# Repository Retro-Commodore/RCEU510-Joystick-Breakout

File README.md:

# RCEU510-Joystick-Breakout
 RCEU510 - Joystick breakout for diagnostics or development purposes

# BOM
1x DB9 Male (for wire)
1x DB9 Female (for wire)
1x 2x5 or 2x 1x5 SIL header

# Description
This little adapter can be used to measure signals (i.e. mouse movements) or diagnostics.

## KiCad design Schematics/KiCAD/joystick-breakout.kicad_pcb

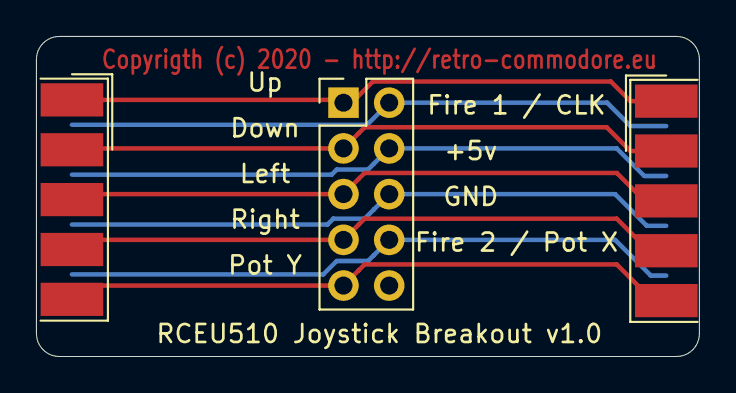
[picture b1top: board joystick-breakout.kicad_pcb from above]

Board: 2 copper layers, 36.8 x 17.8 mm, 3 parts (0 on the bottom side), 9 nets.

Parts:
J1: DB9_Male; DSUB-9_Male_EdgeMount_P2.77mm
J2: Conn_02x05_Top_Bottom_MountingPin; PinHeader_2x05_P2.54mm_Vertical
J3: DB9_Female; DSUB-9_Female_EdgeMount_P2.77mm

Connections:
unnamed: J1.1, J2.1, J3.1
unnamed: J1.2, J2.3, J3.2
unnamed: J1.3, J2.5, J3.3
unnamed: J1.4, J2.7, J3.4
unnamed: J1.5, J2.9, J3.5
unnamed: J1.6, J2.2, J3.6
unnamed: J1.7, J2.4, J3.7
unnamed: J1.8, J2.6, J3.8
unnamed: J1.9, J2.8, J3.9

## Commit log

2020-04-06 Added initial files
    Initial commit
2020-04-06 Renaming dir
2020-04-06 Fixing dirnaming
2021-01-17 Cosmetic changes - added 3d components for 3d view

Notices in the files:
Schematics/KiCAD/joystick-breakout.kicad_pcb:
Copyrigth (c) 2020 - http://retro-commodore.eu
